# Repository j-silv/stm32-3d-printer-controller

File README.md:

# STM32 Nucleo 3D printer controller

This project concerns the replacement of a Teensylu 3D printer controller board for a [uDelta RepRap printer](https://reprap.org/wiki/Micro_Delta). An STM32 NUCLEO-F446RE expansion board (shield) is currently being developed as the replacement. After the board is designed and fabricated, the Marlin open source firmware will be configured for use with the Nucleo board.

# Folder structure

**./kicad/stm32_nucleo_expansion/**
- Contains all the CAD files for the shield PCB

# Power usage
I will be using a [S-240-12 12 V 240 W power supply](https://www.meanwellusa.com/upload/pdf/SP-240/SP-240-spec.pdf) Here is an approximate distribution of the power consumption:

## High power usage

### Pololu stepper motors
- [StepStick from RepRap](https://www.reprap-france.com/produit/363-pilote-de-moteur-pas-a-pas-stepstick)
- Max current of 2 A per coil, with overcurrent output protection at 2.1 A
- On-board current limit via potentiometer needs to be checked (TODO)

### Extruder
- 12 V, 3.5 A (40 W) [as specified here](https://www.reprap-france.com/produit/380-cartouche-de-chauffe-12v-40w)

### Bed
- 12 V, 3.5 A (40 W) [as specified here](https://www.reprap-france.com/produit/1234568345-kit-plateau-chauffant-pour-microdelta-originale)

### Extruder fans
- 12 V, 0.18 A (2.16 W) [as specified here](https://www.reprap-france.com/produit/1234568367-ventilateur-turbine-40x10mm-12v)

## Low power usage

### NUCLEO-F446RE
- Supplied with USB 5 V: [300 mA max input current](https://www.st.com/resource/en/user_manual/um1724-stm32-nucleo64-boards-mb1136-stmicroelectronics.pdf#page=20)
- Supplied with external 12 V: [250 mA max input current](https://www.st.com/resource/en/user_manual/um1724-stm32-nucleo64-boards-mb1136-stmicroelectronics.pdf#page=21)
- Measure current consumed by NUCLEO board via JP5 (TODO)

### Pololu stepper motors
- [Approximately 15 mA consumption](https://www.pololu.com/file/0J450/A4988.pdf) at 3.3 V: 50 mW

### microSD card
- [Approximately 150 mA for standard mode (25 MHz) at 3.3 V](https://images-na.ssl-images-amazon.com/images/I/91tTtUMDM3L.pdf): 500 mW

### LCD
- [Typical 1.1 mA consumption](https://www.openhacks.com/uploadsproductos/eone-1602a1.pdf). At 5 V: 5 mW

# PCB
The shield is a 2-layer board fabricated by JLCPCB. It plugs directly into the NUCLEO-F446RE via two 38-pin morpho connectors.

# Acknowledgments

- Design inspired by [Teensylu RepRap](https://reprap.org/wiki/Teensylu/fr)
- Kudos to [mobilinkd](https://github.com/mobilinkd/stm-morpho-template) for the STM32 morpho connector template
- Kudos to [bettak](https://grabcad.com/library/reprap-stepstick-stepper-motor-driver-module-1) for the RepRap StepStick 3D model
- Thanks to [r/PrintedCircuitBoard on Reddit](https://www.reddit.com/r/PrintedCircuitBoard/) for the advice and comments

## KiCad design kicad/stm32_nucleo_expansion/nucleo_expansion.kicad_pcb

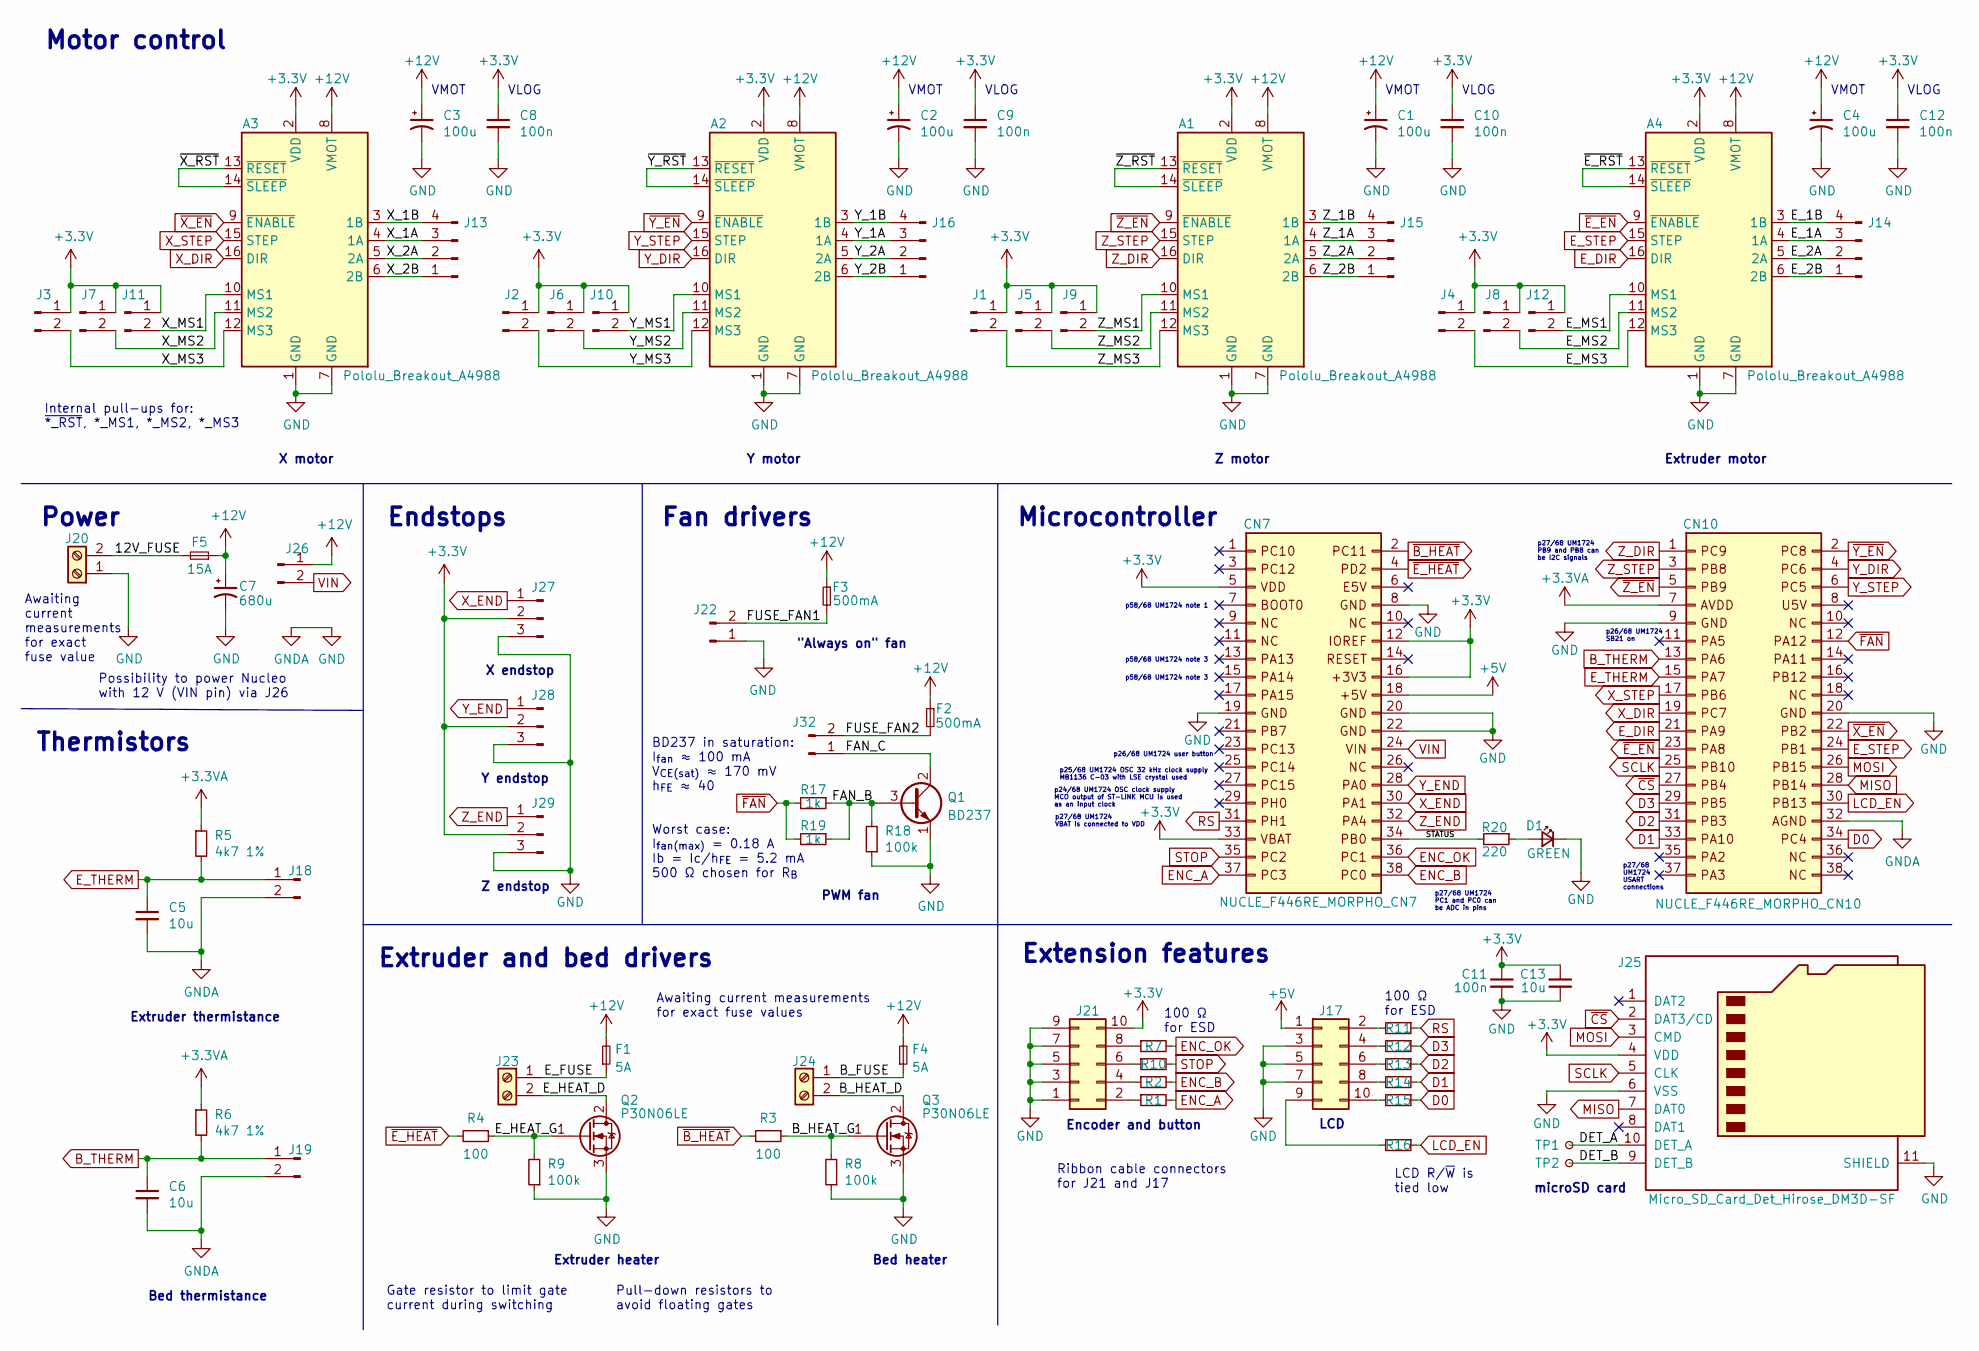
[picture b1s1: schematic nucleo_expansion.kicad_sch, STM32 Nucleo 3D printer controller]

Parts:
A1, A2, A3, A4: Pololu_Breakout_A4988; Pololu_Breakout-16_15.2x20.3mm
C1, C2, C3, C4: 100u; CP_Radial_D5.0mm_P2.00mm; DigiKey ID 399-6102-ND
C5, C6, C13: 10u; C_0805_2012Metric_Pad1.18x1.45mm_HandSolder; DigiKey ID 1276-1096-1-ND
C7: 680u; CP_Radial_D10.0mm_P5.00mm; DigiKey ID 732-8638-1-ND
C8, C9, C10, C11, C12: 100n; C_0805_2012Metric_Pad1.18x1.45mm_HandSolder; DigiKey ID 1276-1003-1-ND
CN7: NUCLE_F446RE_MORPHO_CN7; PinSocket_2x19_P2.54mm_Vertical; DigiKey ID S7122-ND
CN10: NUCLE_F446RE_MORPHO_CN10; PinSocket_2x19_P2.54mm_Vertical; DigiKey ID S7122-ND
D1: GREEN; LED_D3.0mm
F1, F4: 5A; Fuse_0603_1608Metric_Pad1.05x0.95mm_HandSolder; DigiKey ID 2315-FMC16502WHTPCT-ND
F2, F3: 500mA; Fuse_0603_1608Metric_Pad1.05x0.95mm_HandSolder; DigiKey ID 2315-FMC16501WHTPCT-ND
F5: 15A; 3586_mini; DigiKey ID 36-3586-ND and F11955-ND
J1, J2, J3, J4, J5, J6, J7, J8, J9, J10, J11, J12, J18, J19, J26: Conn_01x02_Male; PinHeader_1x02_P2.54mm_Vertical
J13, J14, J15, J16: Conn_01x04_Male; Molex_KK-254_AE-6410-04A_1x04_P2.54mm_Vertical; DigiKey ID WM19478-ND
J17, J21: Conn_02x05_Counter_Clockwise; PinHeader_2x05_P2.54mm_Vertical
J20, J23, J24: Screw_Terminal_01x02; 691137710002; DigiKey ID 732-10955-ND
J22, J32: Conn_01x02_Male; Molex_KK-254_AE-6410-02A_1x02_P2.54mm_Vertical; DigiKey ID WM19485-ND
J25: Micro_SD_Card_Det_Hirose_DM3D-SF; microSD_HC_Hirose_DM3D-SF; DigiKey ID H126097CT-ND
J27, J28, J29: Conn_01x03_Male; Molex_KK-254_AE-6410-03A_1x03_P2.54mm_Vertical; DigiKey ID WM2792-ND
Q1: BD237; TO-126-3_Vertical
Q2, Q3: P30N06LE; TO-220-3_Vertical
R1, R2, R3, R4, R7, R10, R11, R12, R13, R14, R15, R16: 100; R_0805_2012Metric_Pad1.20x1.40mm_HandSolder; DigiKey ID RHM100KCT-ND
R5, R6: 4k7 1%; R_0805_2012Metric_Pad1.20x1.40mm_HandSolder; DigiKey ID A129546CT-ND
R8, R9, R18: 100k; R_0805_2012Metric_Pad1.20x1.40mm_HandSolder; DigiKey ID RHM100KKCT-ND
R17, R19: 1k; R_0805_2012Metric_Pad1.20x1.40mm_HandSolder; DigiKey ID RNCP0805FTD1K00CT-ND
R20: 220; R_0805_2012Metric_Pad1.20x1.40mm_HandSolder
TP1, TP2: TestPoint_Small; TestPoint_Pad_D1.0mm

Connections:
+3.3VA: CN10.7, R5.1, R6.1
+3V3: A1.2 (VDD), A2.2 (VDD), A3.2 (VDD), A4.2 (VDD), C8.1, C9.1, C10.1, C11.1, C12.1, C13.1, CN7.5, CN7.12, CN7.16, CN7.33, J1.1, J2.1, J3.1, J4.1, J5.1, J6.1, J7.1, J8.1, J9.1, J10.1, J11.1, J12.1, J21.10, J25.4 (VDD), J27.2, J28.2, J29.2
+5V: CN7.18, J17.1
+12V: A1.8 (VMOT), A2.8 (VMOT), A3.8 (VMOT), A4.8 (VMOT), C1.1, C2.1, C3.1, C4.1, C7.1, F1.2, F2.1, F3.1, F4.2, F5.1, J26.1
/12V_FUSE: F5.2, J20.2
/B_FUSE: F4.1, J24.1
/B_HEAT_D: J24.2, Q3.2 (D)
/B_HEAT_G: Q3.1 (G), R3.1, R8.2
/DET_A: J25.10 (DET_A), TP1.1
/DET_B: J25.9 (DET_B), TP2.1
/E_1A: A4.4 (1A), J14.3
/E_1B: A4.3 (1B), J14.4
/E_2A: A4.5 (2A), J14.2
/E_2B: A4.6 (2B), J14.1
/E_FUSE: F1.1, J23.1
/E_HEAT_D: J23.2, Q2.2 (D)
/E_HEAT_G: Q2.1 (G), R4.1, R9.2
/E_MS1: A4.10 (MS1), J12.2
/E_MS2: A4.11 (MS2), J8.2
/E_MS3: A4.12 (MS3), J4.2
/FAN_B: Q1.3 (B), R17.1, R18.2, R19.1
/FAN_C: J32.1, Q1.2 (C)
/FUSE_FAN1: F3.2, J22.2
/FUSE_FAN2: F2.2, J32.2
/STATUS: CN7.34, R20.2
/X_1A: A3.4 (1A), J13.3
/X_1B: A3.3 (1B), J13.4
/X_2A: A3.5 (2A), J13.2
/X_2B: A3.6 (2B), J13.1
/X_MS1: A3.10 (MS1), J11.2
/X_MS2: A3.11 (MS2), J7.2
/X_MS3: A3.12 (MS3), J3.2
/Y_1A: A2.4 (1A), J16.3
/Y_1B: A2.3 (1B), J16.4
/Y_2A: A2.5 (2A), J16.2
/Y_2B: A2.6 (2B), J16.1
/Y_MS1: A2.10 (MS1), J10.2
/Y_MS2: A2.11 (MS2), J6.2
/Y_MS3: A2.12 (MS3), J2.2
/Z_1A: A1.4 (1A), J15.3
/Z_1B: A1.3 (1B), J15.4
/Z_2A: A1.5 (2A), J15.2
/Z_2B: A1.6 (2B), J15.1
/Z_MS1: A1.10 (MS1), J9.2
/Z_MS2: A1.11 (MS2), J5.2
/Z_MS3: A1.12 (MS3), J1.2
/~E_RST: A4.13 (~RESET), A4.14 (~SLEEP)
/~X_RST: A3.13 (~RESET), A3.14 (~SLEEP)
/~Y_RST: A2.13 (~RESET), A2.14 (~SLEEP)
/~Z_RST: A1.13 (~RESET), A1.14 (~SLEEP)
B_THERM: C6.1, CN10.13, J19.1, R6.2
D0: CN10.34, R15.1
D1: CN10.33, R14.1
D2: CN10.31, R13.1
D3: CN10.29, R12.1
ENC_A: CN7.37, R1.2
ENC_B: CN7.38, R2.2
ENC_OK: CN7.36, R7.2
E_DIR: A4.16 (DIR), CN10.21
E_STEP: A4.15 (STEP), CN10.24
E_THERM: C5.1, CN10.15, J18.1, R5.2
GND: A1.1 (GND), A1.7 (GND), A2.1 (GND), A2.7 (GND), A3.1 (GND), A3.7 (GND), A4.1 (GND), A4.7 (GND), C1.2, C2.2, C3.2, C4.2, C5.2, C6.2, C7.2, C8.2, C9.2, C10.2, C11.2, C12.2, C13.2, CN7.8, CN7.19, CN7.20, CN7.22, CN10.9, CN10.20, CN10.32, D1.1 (K), J17.3, J17.5, J17.7, J18.2, J19.2, J20.1, J21.1, J21.3, J21.5, J21.7, J21.9, J22.1, J25.6 (VSS), J25.11 (SHIELD), J27.3, J28.3, J29.3, Q1.1 (E), Q2.3 (S), Q3.3 (S), R8.1, R9.1, R18.1; also elsewhere on the board
LCD_EN: CN10.30, R16.1
MISO: CN10.28, J25.7 (DAT0)
MOSI: CN10.26, J25.3 (CMD)
unnamed: D1.2 (A), R20.1
unnamed: J17.2, R11.2
unnamed: J17.4, R12.2
unnamed: J17.6, R13.2
unnamed: J17.8, R14.2
unnamed: J17.9, R16.2
unnamed: J17.10, R15.2
unnamed: J21.8, R7.1
unnamed: J21.2, R1.1
unnamed: J21.4, R2.1
unnamed: J21.6, R10.1
RS: CN7.31, R11.1
SCLK: CN10.25, J25.5 (CLK)
STOP: CN7.35, R10.2
VIN: CN7.24, J26.2
X_DIR: A3.16 (DIR), CN10.19
X_END: CN7.30, J27.1
X_STEP: A3.15 (STEP), CN10.17
Y_DIR: A2.16 (DIR), CN10.4
Y_END: CN7.28, J28.1
Y_STEP: A2.15 (STEP), CN10.6
Z_DIR: A1.16 (DIR), CN10.1
Z_END: CN7.32, J29.1
Z_STEP: A1.15 (STEP), CN10.3
~B_HEAT: CN7.2, R3.2
~CS: CN10.27, J25.2 (DAT3/CD)
~E_EN: A4.9 (~ENABLE), CN10.23
~E_HEAT: CN7.4, R4.2
~FAN: CN10.12, R17.2, R19.2
~X_EN: A3.9 (~ENABLE), CN10.22
~Y_EN: A2.9 (~ENABLE), CN10.2
~Z_EN: A1.9 (~ENABLE), CN10.5

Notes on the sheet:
100 Ω for ESD
VMOT
Extension features
Pull-down resistors to avoid floating gates
"Always on" fan
VLOG
p27/68 UM1724 PC1 and PC0 can be ADC in pins
Extruder motor
p24/68 UM1724 OSC clock supply MCO output of ST-LINK MCU is used as an input clock
X motor
LCD R/~{W} is tied low
BD237 in saturation: I_{fan} ≈ 100 mA V_{CE(sat)} ≈ 170 mV h_{FE} ≈ 40 Worst case: I_{fan(max)} = 0.18 A Ib = Ic/h_{FE} = 5.2 mA 500 Ω chosen for R_{B}
Awaiting current measurements for exact fuse values
Encoder and button
Possibility to power Nucleo with 12 V (VIN pin) via J26
p27/68 UM1724 USART connections
Thermistors
Y endstop
LCD
Fan drivers
p26/68 UM1724 SB21 on
p27/68 UM1724 VBAT is connected to VDD
Bed heater
Gate resistor to limit gate current during switching
microSD card
Ribbon cable connectors for J21 and J17
p27/68 UM1724 PB9 and PB8 can be I2C signals
PWM fan
Extruder and bed drivers
p58/68 UM1724 note 1
Z endstop
Bed thermistance
Endstops
p58/68 UM1724 note 3
Y motor
Extruder heater
Extruder thermistance
Microcontroller
Motor control
Power

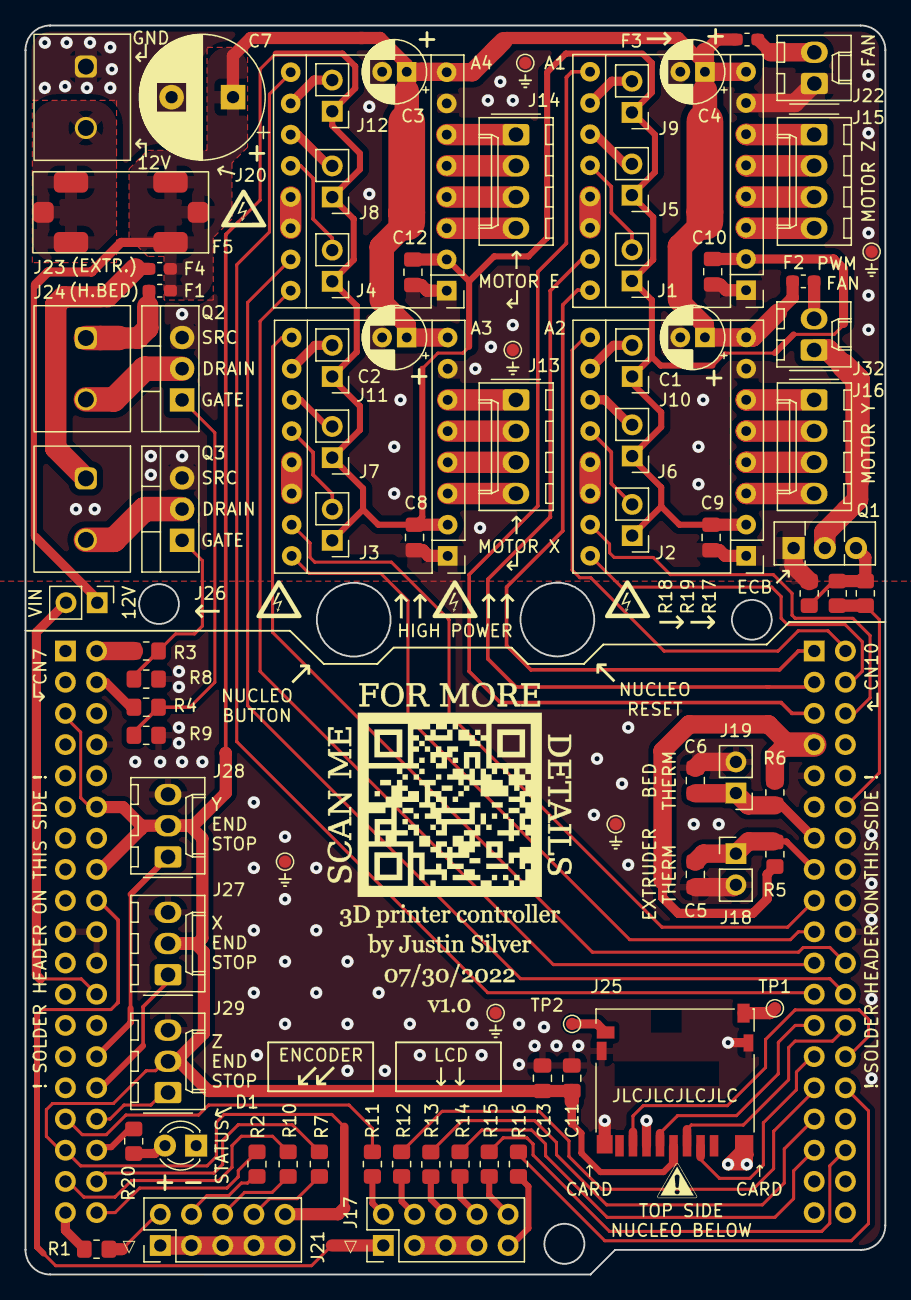
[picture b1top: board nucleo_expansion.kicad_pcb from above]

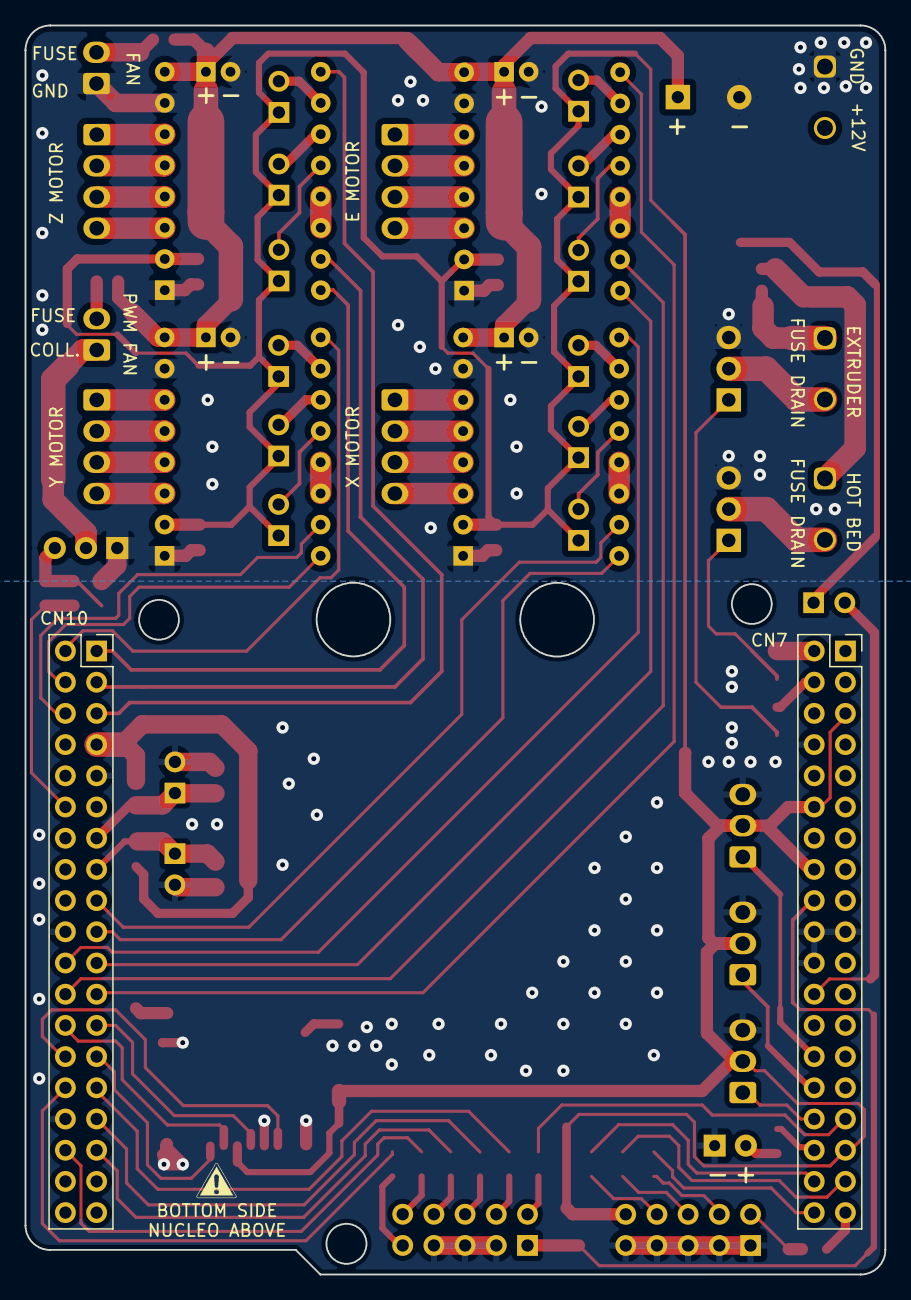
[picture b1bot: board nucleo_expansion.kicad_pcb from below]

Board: 2 copper layers, 70.0 x 101.7 mm, 86 parts (2 on the bottom side), 97 nets.

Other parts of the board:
⏚: TestPoint_Pad_D1.0mm
⏚#2, ⏚#3, ⏚#4, ⏚#5, ⏚#6: TestPoint_Pad_D1.0mm

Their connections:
GND: ⏚.1, ⏚#2.1, ⏚#3.1, ⏚#4.1, ⏚#5.1, ⏚#6.1; also elsewhere on the board

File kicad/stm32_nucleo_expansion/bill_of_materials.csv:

Item,Qty,Reference(s),Value,DigiKey ID,Product
1,4,"A1, A2, A3, A4",Pololu_Breakout_A4988,,STEPPER-DRIVER-STEPSTICKS-A4988
2,4,"C1, C2, C3, C4",100u,399-6102-ND,ESK107M025AC3AA
3,3,"C5, C6, C13",10u,1276-1096-1-ND,CL21A106KOQNNNE
4,1,C7,680u,732-8638-1-ND,860010475015
5,5,"C8, C9, C10, C11, C12",100n,1276-1003-1-ND,CL21B104KBCNNNC
6,1,CN7,NUCLE_F446RE_MORPHO_CN7,S7122-ND,PPPC192LFBN-RC
7,1,CN10,NUCLE_F446RE_MORPHO_CN10,S7122-ND,PPPC192LFBN-RC
8,1,D1,GREEN,,
9,2,"F1, F4",5A,2315-FMC16502WHTPCT-ND,FMC16502WHTP
10,2,"F2, F3",500mA,2315-FMC16501WHTPCT-ND,FMC16501WHTP
11,1,F5,15A,36-3586-ND and F11955-ND,3586 and 0297015.WXT
12,15,"J1, J2, J3, J4, J5, J6, J7, J8, J9, J10, J11, J12, J18, J19, J26",Conn_01x02_Male,,
13,4,"J13, J14, J15, J16",Conn_01x04_Male,WM19478-ND,22280040
14,2,"J17, J21",Conn_02x05_Counter_Clockwise,,
15,3,"J20, J23, J24",Screw_Terminal_01x02,732-10955-ND,691137710002
16,2,"J22, J32",Conn_01x02_Male,WM19485-ND,22281020
17,1,J25,Micro_SD_Card_Det_Hirose_DM3D-SF,H126097CT-ND,DM3D-SF(41)
18,3,"J27, J28, J29",Conn_01x03_Male,WM2792-ND,22280030
19,1,Q1,BD237,,BD237
20,2,"Q2, Q3",P30N06LE,,P30N06LE
21,12,"R1, R2, R3, R4, R7, R10, R11, R12, R13, R14, R15, R16",100,RHM100KCT-ND,ESR10EZPJ101
22,2,"R5, R6",4k7 1%,A129546CT-ND,CRGH0805F4K7
23,3,"R8, R9, R18",100k,RHM100KKCT-ND,ESR10EZPJ104
24,2,"R17, R19",1k,RNCP0805FTD1K00CT-ND,RNCP0805FTD1K00
25,1,R20,220,,
26,2,"TP1, TP2",TestPoint_Small,,

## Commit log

2022-07-23 Initial commit - add all CAD files
    v1.0 of PCB
2022-07-23 Add schematic pdf and clear ERC markers
2022-07-23 Add Gerber output files
2022-07-24 Clean up schematic and PCB
2022-07-24 Update Gerber files
2022-07-31 Update schematic, PCB, and README (fab send-off v1.0)
    SCHEMATIC:
    - Clean up, rearrange some parts of the schematic
    - Replace one of the "always on" fans with a PWM control using a BJT (BD237)
    - Add fuses for fans
    - Add fuse for main power (SMT fuse blade holder)
    - Add fuse for extruder
2022-07-31 Add images (schematic, PCB) and .gitignore file

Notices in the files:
parts and their libraries:
Copyright 2021 Accelerated Designs. All rights reserved.
